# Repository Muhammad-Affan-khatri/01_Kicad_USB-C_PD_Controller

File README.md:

# 01_Kicad_USB-C_PD_Controller
Autonomous USB-C PD trigger board using the WCH CH224K. It requests 5/9/12/15/20 V from a PD charger and outputs it on 4 mm banana jacks. Designed in KiCad.

# USB-C PD Trigger Board (CH224K)

A compact, MCU-free USB Power Delivery trigger board. The CH224K negotiates the requested voltage (5, 9, 12, 15 or 20 V) with a PD charger, and the board outputs it on 4 mm banana jacks for use as a simple bench supply. A jumper header on the CFG1 pin selects the voltage, and a status LED on the PG pin shows when negotiation has succeeded.

**Controller:** WCH CH224K (ESSOP-10), configured by resistor or level selection
**Input:** USB-C receptacle
**Output:** 4 mm banana jacks (VBUS/GND)
**Tools:** KiCad, 2-layer PCB, targeted at JLCPCB fabrication

**Status:** Design stage Completed. The schematic and layout are drawn complete but not yet fabricated or tested physically. 

**Roadmap:** V2 will add an STM32 and OLED display for MCU-controlled voltage selection.

**Libraries used:**
1) kicad default - most of the packages.
2) sparkfun - USB type C receptacle (needs to be installed via kicad's plugin & library manager).

# Schematics Capture

# PCB Design

# 3D Model

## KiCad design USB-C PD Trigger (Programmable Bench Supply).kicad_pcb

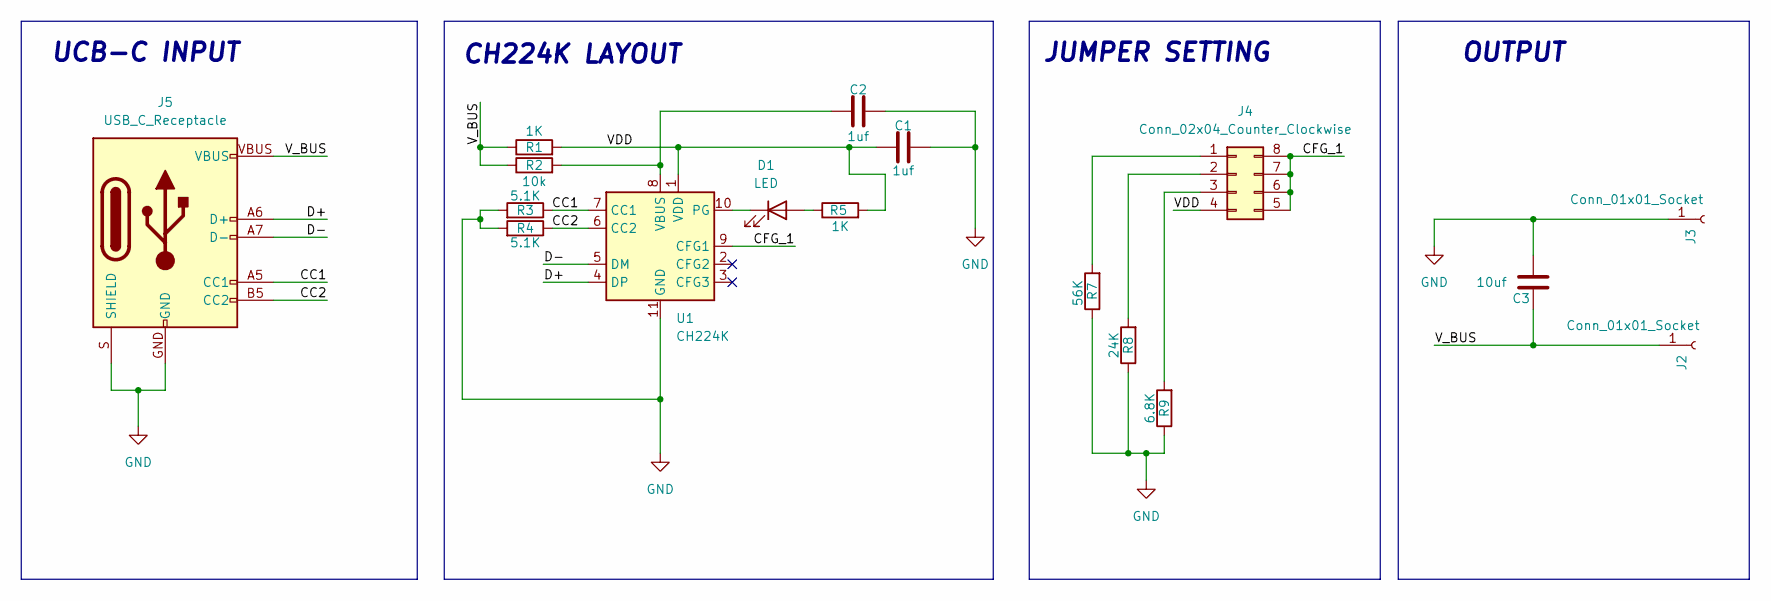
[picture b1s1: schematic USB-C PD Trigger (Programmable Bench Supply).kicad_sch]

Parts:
C1, C2: 1uf; C_0603_1608Metric_Pad1.08x0.95mm_HandSolder
C3: 10uf; C_0805_2012Metric_Pad1.18x1.45mm_HandSolder
D1: LED; LED_0603_1608Metric
J2, J3: Conn_01x01_Socket; Banana_Cliff_FCR7350B_S16N-PC_Horizontal
J4: Conn_02x04_Counter_Clockwise; PinHeader_2x04_P2.00mm_Vertical
J5: USB_C_Receptacle; USB-C_16
R1, R5: 1K; R_0603_1608Metric_Pad0.98x0.95mm_HandSolder
R2: 10k; R_0603_1608Metric_Pad0.98x0.95mm_HandSolder
R3, R4: 5.1K; R_0603_1608Metric_Pad0.98x0.95mm_HandSolder
R7: 56K; R_0603_1608Metric_Pad0.98x0.95mm_HandSolder
R8: 24K; R_0603_1608Metric_Pad0.98x0.95mm_HandSolder
R9: 6.8K; R_0603_1608Metric_Pad0.98x0.95mm_HandSolder
U1: CH224K; SSOP-10-1EP_3.9x4.9mm_P1mm_EP2.1x3.3mm

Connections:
/CC1: J5.A5 (CC1), R3.1, U1.7 (CC1)
/CC2: J5.B5 (CC2), R4.1, U1.6 (CC2)
/CFG_1: J4.5, J4.6, J4.7, J4.8, U1.9 (CFG1)
/D+: J5.A6 (D+), J5.B6 (D+), U1.4 (DP)
/D-: J5.A7 (D-), J5.B7 (D-), U1.5 (DM)
/VDD: C1.1, J4.4, R1.2, R5.2, U1.1 (VDD)
/V_BUS: C3.2, J2.1 (Pin_1_1), J5.VBUS, R1.1, R2.1
GND: C1.2, C2.2, C3.1, J3.1 (Pin_1_1), J5.GND, J5.S (SHIELD), R3.2, R4.2, R7.1, R8.1, R9.1, U1.11 (GND)
unnamed: D1.2 (A), R5.1
unnamed: D1.1 (K), U1.10 (PG)
unnamed: J4.1, R7.2
unnamed: J4.2, R8.2
unnamed: J4.3, R9.2
unnamed: C2.1, R2.2, U1.8 (VBUS)

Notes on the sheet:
UCB-C INPUT
CH224K LAYOUT
JUMPER SETTING
OUTPUT

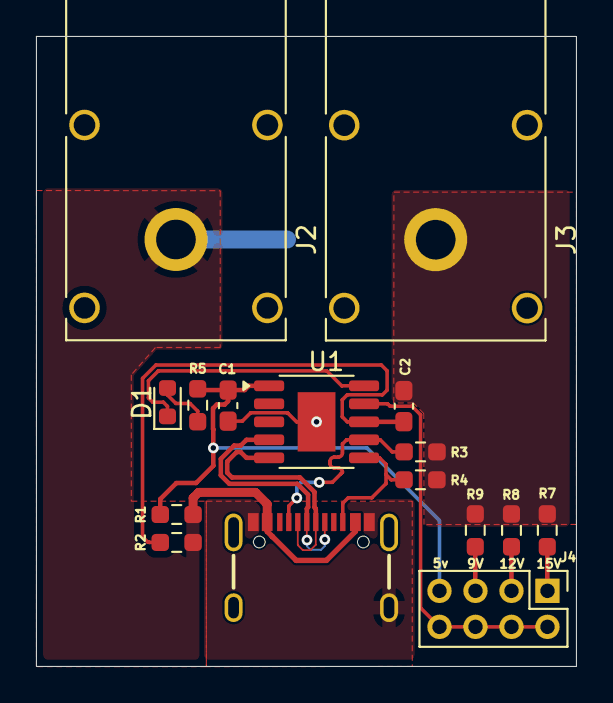
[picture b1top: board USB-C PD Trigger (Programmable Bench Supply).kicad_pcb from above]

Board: 2 copper layers, 30.0 x 35.0 mm, 17 parts (1 on the bottom side), 14 nets.
